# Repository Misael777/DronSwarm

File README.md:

# DronSwarm

Proyecto mecatrónico para diseñar y fabricar drones propios de bajo costo para minería y operarlos en enjambre con control avanzado.

- **DS-I (inspección):** compite con DJI Matrice 4E. Target: ≤ US$1,500, ≥ 35 min a 4,500 msnm, IP54.
- **DS-D (delivery):** compite con DJI Matrice 400. Target: ≤ US$3,500, 5 kg a 4,500 msnm.
- **Diferenciadores:** operación a ≥ 5,000 msnm, enjambre nativo, ecosistema abierto (PX4), sin licencias.

## Probar

```bash
./dronswarm.sh        # consola de pruebas: simulaciones, CAD, plan y diagnóstico
```
Detalle en [docs/como-probar.md](docs/como-probar.md).

## Documentos clave

| Documento | Para qué |
|---|---|
| [docs/plan/DronSwarm_Plan_de_Trabajo.xlsx](docs/plan/DronSwarm_Plan_de_Trabajo.xlsx) | Seguimiento del plan (24 sprints) |
| [docs/plan/PLAN_DE_TRABAJO.md](docs/plan/PLAN_DE_TRABAJO.md) | Plan técnico detallado |
| [docs/guia-estructura-repo.md](docs/guia-estructura-repo.md) | Estructura y convenciones |
| [docs/decisiones.md](docs/decisiones.md) | Decisiones técnicas (ADR) |
| [docs/setup-wsl.md](docs/setup-wsl.md) | Instalación del entorno |

## Estructura

`engineering/` cálculos · `simulation/` PX4 + Gazebo · `control/` enjambre y misiones · `cad/` OpenSCAD + FreeCAD ·
`electronics/` · `manufacturing/` · `hardware/` · `app/` · `tools/` · `docs/`

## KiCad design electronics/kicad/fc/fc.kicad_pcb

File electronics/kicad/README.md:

# E6 · Placas en KiCad

> Flujo: esquema SKIDL → netlist (`electronics/build_netlists.sh`) → placa (`make_boards.py`) → ruteo (`route_boards.py`,
> Freerouting) → DRC (`kicad-cli`) → fabricación (`fab_outputs.sh`, se niega si el DRC no está limpio).
> Abrir cada placa con KiCad 8: `electronics/kicad/<placa>/<placa>.kicad_pro` (la biblioteca `DronSwarm` se carga sola).

## Estado (2026-10-26)

| Placa | Piezas | Contorno actual · meta [mm] | Estado | Falta |
|---|---|---|---|---|
| GNSS (`gnss`) | 32 | 40 × 40 · 40 × 40 | **ruteada**: 0 errores de DRC, 1 conexión de 3V3 por cerrar; RF en microcinta de 0.36 mm ruteada a mano por script | cerrar 1 conexión, revisión humana, Gerber |
| BMS 6S (`bms_ds_i`) | 105 | 60 × 51 · 60 × 40 | colocada, nets asignadas | ruteo manual (el autorruteador dejó 27 pendientes) |
| BMS 12S (`bms_ds_d`) | 141 | 80 × 46 · 80 × 45 | colocada, nets asignadas | ruteo manual (el autorruteador no terminó en 1 h) |
| Controladora (`fc`) | 165 | 55 × 73 · 55 × 45 | colocada en dos caras, nets asignadas | colocación densa con conectores al borde y ruteo manual |
| ESC 4 en 1 DS-I (`esc_ds_i`) | 335 | 60 × 88 · 60 × 60 | colocada, nets asignadas | colocación de potencia (transistores en dos caras) y ruteo manual |
| ESC GaN DS-D (`esc_ds_d`) | 115 | 40 × 70 · 40 × 70 | colocada; **faltan las 3 huellas del LMG1210** | plano RVR0019A de TI, colocación del lazo GaN, ruteo manual |
| Cargador GaN (`charger`) | 131 | 100 × 80 · 100 × 80 | colocada; **faltan las 2 huellas del LMG1210** | ídem |

La colocación automática agrupa por subcircuito y pone los pasivos chicos abajo, pero **no está optimizada**: es el
punto de partida para colocar a mano en KiCad. El ruteo automático sirve para placas chicas de señal (GNSS); en las de
potencia y en las densas no converge y además no conviene: el lazo de conmutación se rutea a mano.

## Biblioteca `DronSwarm.pretty` (`gen_footprints.py`, desde las hojas de datos)

| Huella | Fuente |
|---|---|
| `EPC2302_QFN-3x5mm` | EPC2302: cobre, aberturas de máscara (máscara definida por soldadura) y esténcil, págs. 11-12 |
| `Bosch_LGA-16_3x4.5mm_P0.5mm` | BMI088, fig. 11 |
| `Quectel_LG290P_LGA-79_12.2x16mm` | LG290P(03) Hardware Design, fig. 18 (cortesía de 3 mm alrededor del módulo, como pide Quectel) |
| `Pad_Power_4x3mm`, `6x4mm`, `8x5mm` | pads para soldar cables de potencia |
| **`TI_WQFN-19_RVR0019A_4x3mm`** | **PENDIENTE**: la hoja SNOSD12D del LMG1210 no trae el dibujo mecánico; bajar el plano RVR0019A desde la página del producto en ti.com y agregarlo a `gen_footprints.py` |

## Reglas de las placas

- 4 capas: señal / GND (In1) / alimentación (In2) / señal. Clase **Potencia** 1.0 mm; **RF50** 0.36 mm (GNSS).
- **Placas de 12S a 5,000 msnm** (ESC DS-D, BMS DS-D, cargador): IPC-2221 pide 1.5 mm entre conductores de 51-100 V
  sin recubrimiento por encima de 3,050 m (B3); con **recubrimiento conformado** (B4) bastan 0.13 mm → el recubrimiento
  es obligatorio y está en el presupuesto.
- Lazo de potencia GaN (ESC DS-D, cargador): diseño "vertical" de EPC, con los condensadores de 2.2 µF en la cara
  opuesta, directamente bajo el medio puente, y retorno por In1 (nota de aplicación de EPC sobre el ruteo de GaN).

## Revisión humana antes de fabricar (cada placa)

1. DRC limpio y 0 conexiones pendientes; `bash electronics/kicad/fab_outputs.sh <placa>`.
2. Huellas propias impresas a 1:1 sobre la pieza real.
3. Potencia: ancho de pistas por corriente (IPC-2152), vías térmicas bajo transistores y LDO.
4. RF (GNSS): microcinta de 50 Ω con el stack real del fabricante, plano de GND continuo bajo la línea.
5. Distancias de 12S y recubrimiento conformado anotados en el plano de fabricación.

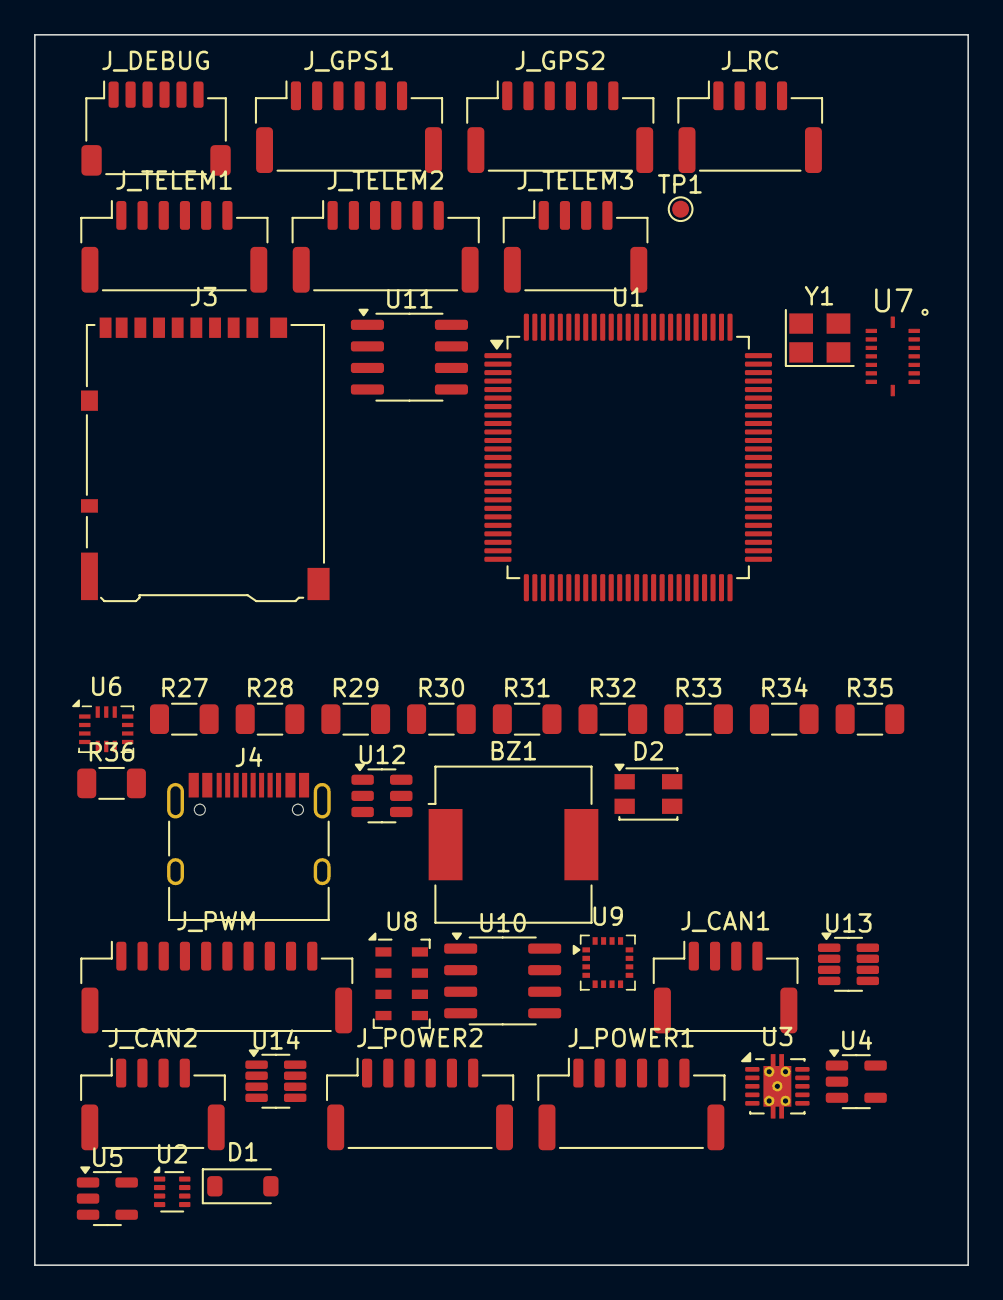
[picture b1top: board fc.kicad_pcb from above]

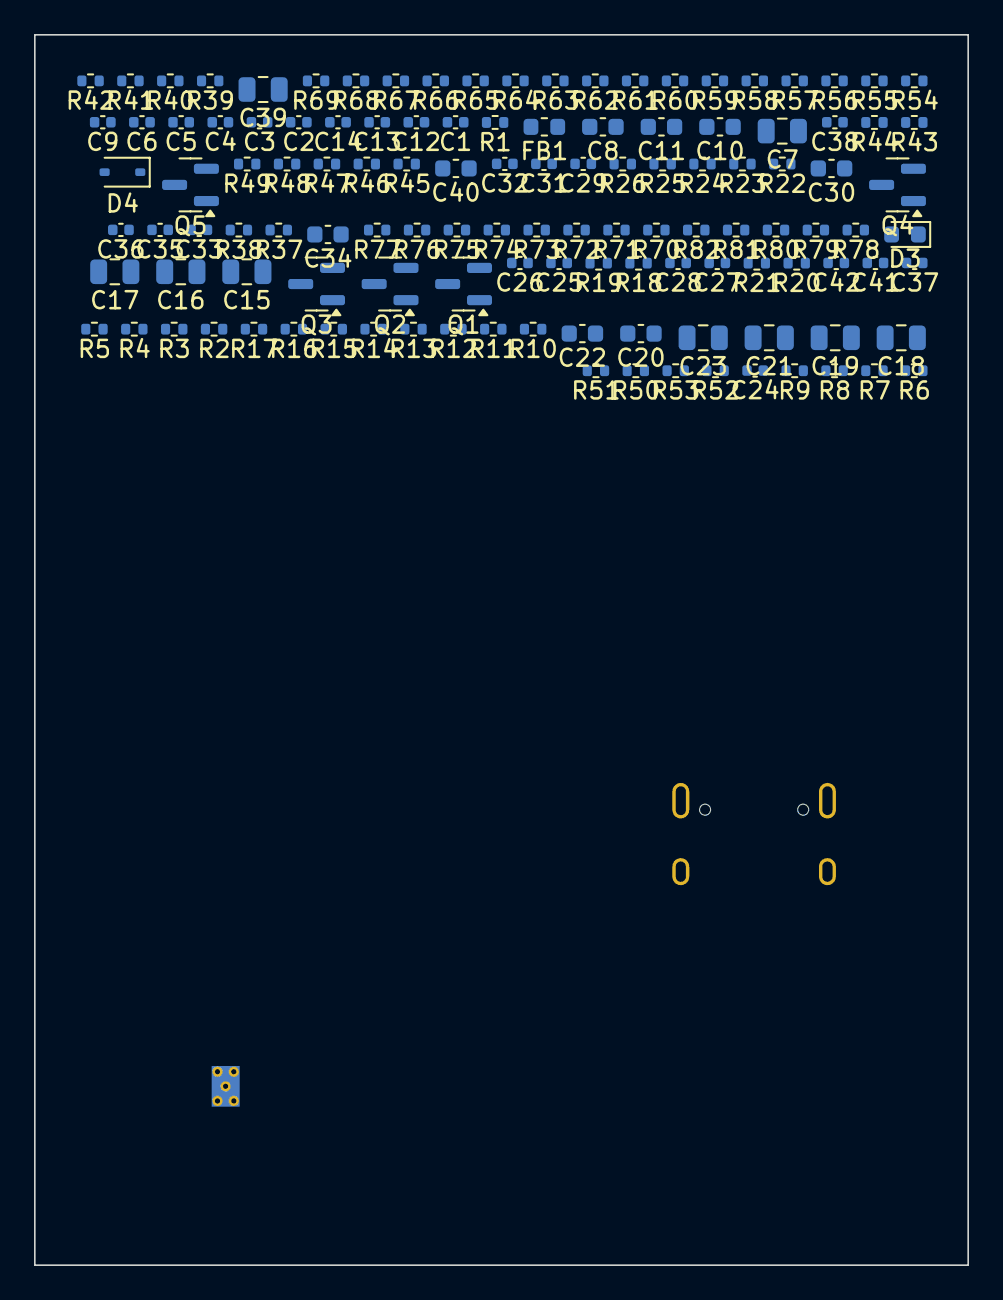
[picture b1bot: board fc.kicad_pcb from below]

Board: 4 copper layers, 55.0 x 72.5 mm, 165 parts (122 on the bottom side), 141 nets, no tracks yet.

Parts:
BZ1: Buzzer; Buzzer_CUI_CPT-9019S-SMT
C1, C2, C3, C4, C5, C6, C9, C12, C24, C25, C26, C27, C28, C29, C31, C32, C33, C35, C36, C37, C38, C41, C42: 100n; C_0402_1005Metric
C7: 4.7u; C_0805_2012Metric
C8, C20, C22, C34: 1u; C_0603_1608Metric
C10, C11, C30: 2.2u; C_0603_1608Metric
C13, C14: 12p/C0G; C_0402_1005Metric
C15, C16, C21, C23, C39: 10u/10V; C_0805_2012Metric
C17, C18, C19: 22u/10V; C_0805_2012Metric
C40: 4.7n/100V; C_0603_1608Metric
D1: PMEG2010; D_SOD-123
D2: LED_RGB; LED_Kingbright_AAA3528ESGCT
D3: verde; LED_0603_1608Metric
D4: BAT54; D_SOD-323
FB1: 600R@100MHz; L_0603_1608Metric
J3: Micro_SD_Card_Det1; microSD_HC_Hirose_DM3AT-SF-PEJM5
J4: USB_C_Receptacle_USB2.0_16P; USB_C_Receptacle_HRO_TYPE-C-31-M-12
J_CAN1, J_CAN2: Conn_01x04; JST_GH_SM04B-GHS-TB_1x04-1MP_P1.25mm_Horizontal
J_DEBUG: Conn_01x06; JST_SH_SM06B-SRSS-TB_1x06-1MP_P1.00mm_Horizontal
J_GPS1, J_GPS2: Conn_01x06; JST_GH_SM06B-GHS-TB_1x06-1MP_P1.25mm_Horizontal
J_POWER1, J_POWER2: Conn_01x06; JST_GH_SM06B-GHS-TB_1x06-1MP_P1.25mm_Horizontal
J_PWM: Conn_01x10; JST_GH_SM10B-GHS-TB_1x10-1MP_P1.25mm_Horizontal
J_RC: Conn_01x04; JST_GH_SM04B-GHS-TB_1x04-1MP_P1.25mm_Horizontal
J_TELEM1, J_TELEM2: Conn_01x06; JST_GH_SM06B-GHS-TB_1x06-1MP_P1.25mm_Horizontal
J_TELEM3: Conn_01x04; JST_GH_SM04B-GHS-TB_1x04-1MP_P1.25mm_Horizontal
Q1, Q2, Q3, Q5: 2N7002; SOT-23
Q4: AO3400A; SOT-23
R1, R3, R4, R5, R6, R7, R8, R9, R13, R14, R16, R17, R22, R23, R24, R39: 10k; R_0402_1005Metric
R2: 35.7k; R_0402_1005Metric
R10: 56k; R_0402_1005Metric
R11, R12, R15, R26, R82: 100k; R_0402_1005Metric
R18, R19, R20, R21, R78, R79, R80: 1k; R_0402_1005Metric
R25, R81: 100; R_0402_1005Metric
R27, R28, R29, R30, R31, R32, R33, R34, R35, R36: 150; R_1206_3216Metric
R37, R38, R50, R51, R52, R53: 2.2k; R_0402_1005Metric
R40, R41, R42, R43, R44: 47k; R_0402_1005Metric
R45, R46: 5.1k; R_0402_1005Metric
R47: 1M; R_0402_1005Metric
R48: 22k; R_0402_1005Metric
R49: 33k; R_0402_1005Metric
R54, R55, R56, R57, R58, R59, R60, R61, R62, R63, R64, R65, R66, R67, R68, R69: 22; R_0402_1005Metric
R70, R71, R72, R73, R74, R75, R76, R77: 47; R_0402_1005Metric
TP1: TestPoint; TestPoint_Pad_D1.0mm
U1: STM32H743VITx; LQFP-100_14x14mm_P0.5mm
U2: TPS2116DRL; SOT-583-8
U3: TPS2561; VSON-10-1EP_3x3mm_P0.5mm_EP1.65x2.4mm_ThermalVias
U4, U5: TLV75533PDBV; SOT-23-5
U6: IIM-42652; Bosch_LGA-14_3x2.5mm_P0.5mm
U7: BMI088; Bosch_LGA-16_3x4.5mm_P0.5mm
U8: MS5611-01BA; LGA-8_3x5mm_P1.25mm
U9: IST8310; LGA-16_3x3mm_P0.5mm
U10: 24LC64; SOIC-8_3.9x4.9mm_P1.27mm
U11: MB85RS256B; SOIC-8_3.9x4.9mm_P1.27mm
U12: USBLC6-2SC6; SOT-23-6
U13, U14: TCAN330; SOT-23-8
Y1: 16MHz 10pF; Crystal_SMD_3225-4Pin_3.2x2.5mm

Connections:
3V3: C1.1, C2.1, C3.1, C4.1, C5.1, C6.1, C7.1, C21.1, C38.1, C39.1, C41.1, C42.1, D2.4, FB1.1, J3.4, J_DEBUG.1, R13.2, R14.2, R39.2, R40.2, R41.2, R42.2, R43.2, R44.2, R50.2, R51.2, R52.2, R53.2, R80.1, U1.6, U1.11, U1.27, U1.50, U1.75, U1.100, U4.5, U11.3, U11.7, U11.8, U13.3, U14.3
3V3_SENSORS: C23.1, C29.1, C30.1, C31.1, C32.1, C33.1, C36.1, C37.1, R22.2, R23.2, R24.2, R37.2, R38.2, U5.5, U6.5, U6.8, U7.3, U7.11, U8.1, U8.2, U9.2, U9.13, U9.14, U10.8
5V: BZ1.1, C17.1, C20.1, C22.1, D1.1, D4.1, R16.1, R27.1, R28.1, R29.1, R30.1, R31.1, R32.1, R33.1, R34.1, R35.1, R36.1, U2.2, U2.7, U3.2, U3.3, U4.1, U4.3, U5.1
5V_HIPOWER: C19.1, J_CAN1.1, J_CAN2.1, U3.8
5V_PERIPH: C18.1, J_GPS1.1, J_GPS2.1, J_RC.1, J_TELEM1.1, J_TELEM2.1, J_TELEM3.1, U3.9
BATT1_I: J_POWER1.3, R18.1
BATT1_I_ADC: C25.1, R18.2, U1.32
BATT1_V: J_POWER1.4, R19.1
BATT1_V_ADC: C26.1, R19.2, U1.33
BATT2_I: J_POWER2.3, R20.1
BATT2_I_ADC: C27.1, R20.2, U1.24
BATT2_V: J_POWER2.4, R21.1
BATT2_V_ADC: C28.1, R21.2, U1.35
BRICK1_5V: C15.1, J_POWER1.1, J_POWER1.2, R2.1, R4.1, U2.3, U2.5
BRICK2_5V: C16.1, J_POWER2.1, J_POWER2.2, R6.1, U2.6
BUZZ_D: BZ1.2, D4.2, Q5.3
BUZZ_G: Q5.1, R81.2, R82.1
CAN1_H: J_CAN1.2, U13.7
CAN1_L: J_CAN1.3, U13.6
CAN2_H: J_CAN2.2, U14.7
CAN2_L: J_CAN2.3, U14.6
DET_BRICK1_5V: Q1.1, R4.2, R5.1
DET_BRICK2_5V: Q2.1, R6.2, R7.1
DET_USB_VBUS: Q3.1, R8.2, R9.1
GND: C1.2, C2.2, C3.2, C4.2, C5.2, C6.2, C7.2, C8.2, C9.2, C10.2, C11.2, C12.2, C13.2, C14.2, C15.2, C16.2, C17.2, C18.2, C19.2, C20.2, C21.2, C22.2, C23.2, C24.2, C25.2, C26.2, C27.2, C28.2, C29.2, C30.2, C31.2, C32.2, C33.2, C34.2, C35.2, C36.2, C37.2, C38.2, C39.2, C40.2, C41.2, C42.2, D3.1, J3.6, J3.10, J4.A1, J4.A12, J4.B1, J4.B12, J_CAN1.4, J_CAN2.4, J_DEBUG.6, J_GPS1.6, J_GPS2.6, J_POWER1.5, J_POWER1.6, J_POWER2.5, J_POWER2.6, J_PWM.9, J_PWM.10, J_RC.4, J_TELEM1.6, J_TELEM2.6, J_TELEM3.4, Q1.2, Q2.2, Q3.2, Q4.2, Q5.2, R1.2, R3.2, R5.2, R7.2, R9.2, R10.2, R11.2, R12.2, R15.2, R17.2, R26.2, R45.2, R46.2, R47.2, R49.2, R82.2, U1.10, U1.19, U1.26, U1.49, U1.74, U1.99, U2.1, U3.1, U3.11, U4.2, U5.2, U6.6, U6.7, U7.2, U7.4, U7.6, U7.7, U8.3, U8.4, U8.5, U9.5, U9.6, U9.9, U9.11, U10.1, U10.2, U10.3, U10.4, U10.7, U11.4, U12.2, U13.2, U13.5, U13.8, U14.2, U14.5, U14.8, Y1.2, Y1.4
HEATER_D: Q4.3, R27.2, R28.2, R29.2, R30.2, R31.2, R32.2, R33.2, R34.2, R35.2, R36.2
HEATER_G: Q4.1, R25.2, R26.1
HSE_IN: C13.1, U1.12, Y1.1
HSE_OUT: C14.1, U1.13, Y1.3
I2C1_SCL: J_GPS1.4, R50.1, U1.95
I2C1_SDA: J_GPS1.5, R51.1, U1.93
I2C2_SCL: J_GPS2.4, R52.1, U1.46
I2C2_SDA: J_GPS2.5, R53.1, U1.47
I2C4_SCL: R37.1, U1.59, U8.8, U9.1, U10.6
I2C4_SDA: R38.1, U1.60, U8.7, U9.16, U10.5
J_GPS1_PA10: J_GPS1.3, R65.2
J_GPS1_PB6: J_GPS1.2, R64.2
J_GPS2_PE0: J_GPS2.3, R67.2
J_GPS2_PE1: J_GPS2.2, R66.2
J_RC_PC6: J_RC.2, R68.2
J_RC_PC7: J_RC.3, R69.2
J_TELEM1_PE7: J_TELEM1.3, R55.2
J_TELEM1_PE8: J_TELEM1.2, R54.2
J_TELEM1_PE9: J_TELEM1.5, R57.2
J_TELEM1_PE10: J_TELEM1.4, R56.2
J_TELEM2_PC8: J_TELEM2.5, R61.2
J_TELEM2_PC9: J_TELEM2.4, R60.2
J_TELEM2_PC12: J_TELEM2.2, R58.2
J_TELEM2_PD2: J_TELEM2.3, R59.2
J_TELEM3_PA3: J_TELEM3.3, R63.2
J_TELEM3_PD5: J_TELEM3.2, R62.2
MUX_PR1: R2.2, R3.1, U2.4
unnamed: R1.1, U1.94
unnamed: Q1.3, U1.77
unnamed: Q2.3, U1.51
unnamed: Q3.3, U1.45
unnamed: R10.1, U3.7
unnamed: R11.1, U1.1, U3.4
unnamed: R12.1, U1.78, U3.5
unnamed: R13.1, U1.2, U3.10
unnamed: R14.1, U1.79, U3.6
unnamed: R15.1, U1.36, U5.3
unnamed: R22.1, U1.7, U6.12
unnamed: U1.5, U6.4
unnamed: R24.1, U1.9, U7.14
unnamed: R23.1, U1.8, U7.5
unnamed: U1.3, U7.16
unnamed: U1.4, U7.12
unnamed: R25.1, U1.96
unnamed: C34.1, U9.10
unnamed: C35.1, U9.7
unnamed: R39.1, U1.85, U11.1
unnamed: U1.84, U11.6
unnamed: U1.18, U11.5
unnamed: U1.17, U11.2
unnamed: J3.5, U1.87
unnamed: J3.3, R40.1, U1.88
unnamed: J3.7, R41.1, U1.53
unnamed: J3.8, R42.1, U1.54
unnamed: J3.1, R43.1, U1.89
unnamed: J3.2, R44.1, U1.90
unnamed: J4.A5, R45.1
unnamed: J4.B5, R46.1
unnamed: U1.82, U13.1
unnamed: U1.81, U13.4
unnamed: U1.52, U14.1
unnamed: U1.91, U14.4
unnamed: R54.1, U1.38
unnamed: R55.1, U1.37
unnamed: R56.1, U1.40
unnamed: R57.1, U1.39
unnamed: R58.1, U1.80
unnamed: R59.1, U1.83
unnamed: R60.1, U1.66
unnamed: R61.1, U1.65
unnamed: R62.1, U1.86
unnamed: R63.1, U1.25
unnamed: R64.1, U1.92
unnamed: R65.1, U1.69
unnamed: R66.1, U1.98
unnamed: R67.1, U1.97
unnamed: R68.1, U1.63
unnamed: R69.1, U1.64
unnamed: J_DEBUG.2, U1.55
unnamed: J_DEBUG.3, U1.56
unnamed: J_DEBUG.4, U1.72
unnamed: J_DEBUG.5, U1.76
unnamed: R70.1, U1.67
unnamed: R71.1, U1.41
unnamed: R72.1, U1.43
unnamed: R73.1, U1.44
unnamed: R74.1, U1.61
unnamed: R75.1, U1.62
unnamed: R76.1, U1.22
unnamed: R77.1, U1.23
unnamed: D2.1, R78.1
unnamed: R78.2, U1.57
unnamed: D2.3, R79.1
unnamed: R79.2, U1.58
unnamed: D3.2, R80.2
unnamed: R81.1, U1.34
NRST: C12.1, TP1.1, U1.14
PWM1: J_PWM.1, R70.2
PWM2: J_PWM.2, R71.2
PWM3: J_PWM.3, R72.2
PWM4: J_PWM.4, R73.2
PWM5: J_PWM.5, R74.2
PWM6: J_PWM.6, R75.2
PWM7: J_PWM.7, R76.2
PWM8: J_PWM.8, R77.2
SCALED_V5: C24.1, R16.2, R17.1, U1.28
SPI1_MISO: U1.30, U6.1, U7.10, U7.15
SPI1_MOSI: U1.31, U6.14, U7.9
SPI1_SCK: U1.29, U6.13, U7.8
USB_DM: J4.A7, J4.B7, U1.70, U12.3, U12.4
USB_DP: J4.A6, J4.B6, U1.71, U12.1, U12.6
USB_SHIELD: C40.1, J4.S1, R47.1
USB_VBUS: D1.2, J4.A4, J4.A9, J4.B4, J4.B9, R8.1, R48.1, U12.5
USB_VBUS_SENSE: R48.2, R49.1, U1.68
VCAP: C10.1, C11.1, U1.48, U1.73
VDDA: C8.1, C9.1, FB1.2, U1.20, U1.21

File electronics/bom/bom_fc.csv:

Comment,Designator,Footprint,Quantity,Unit price USD (est.)
100n,"C1,C2,C3,C4,C5,C6,C9,C12,C24,C25,C26,C27,C28,C29,C31,C32,C33,C35,C36,C37,C38,C41,C42",Capacitor_SMD:C_0402_1005Metric,23,0.004
10k,"R1,R3,R4,R5,R6,R7,R8,R9,R13,R14,R16,R17,R22,R23,R24,R39",Resistor_SMD:R_0402_1005Metric,16,0.002
22,"R54,R55,R56,R57,R58,R59,R60,R61,R62,R63,R64,R65,R66,R67,R68,R69",Resistor_SMD:R_0402_1005Metric,16,0.002
150,"R27,R28,R29,R30,R31,R32,R33,R34,R35,R36",Resistor_SMD:R_1206_3216Metric,10,0.008
47,"R70,R71,R72,R73,R74,R75,R76,R77",Resistor_SMD:R_0402_1005Metric,8,0.002
1k,"R18,R19,R20,R21,R78,R79,R80",Resistor_SMD:R_0402_1005Metric,7,0.002
2.2k,"R37,R38,R50,R51,R52,R53",Resistor_SMD:R_0402_1005Metric,6,0.002
Conn_01x06,"J_GPS1,J_GPS2,J_POWER1,J_POWER2,J_TELEM1,J_TELEM2",Connector_JST:JST_GH_SM06B-GHS-TB_1x06-1MP_P1.25mm_Horizontal,6,0.24
100k,"R11,R12,R15,R26,R82",Resistor_SMD:R_0402_1005Metric,5,0.002
10u/10V,"C15,C16,C21,C23,C39",Capacitor_SMD:C_0805_2012Metric,5,0.03
47k,"R40,R41,R42,R43,R44",Resistor_SMD:R_0402_1005Metric,5,0.002
1u,"C8,C20,C22,C34",Capacitor_SMD:C_0603_1608Metric,4,0.008
2N7002,"Q1,Q2,Q3,Q5",Package_TO_SOT_SMD:SOT-23,4,0.02
Conn_01x04,"J_CAN1,J_CAN2,J_RC,J_TELEM3",Connector_JST:JST_GH_SM04B-GHS-TB_1x04-1MP_P1.25mm_Horizontal,4,0.2
2.2u,"C10,C11,C30",Capacitor_SMD:C_0603_1608Metric,3,0.008
22u/10V,"C17,C18,C19",Capacitor_SMD:C_0805_2012Metric,3,0.03
100,"R25,R81",Resistor_SMD:R_0402_1005Metric,2,0.002
12p/C0G,"C13,C14",Capacitor_SMD:C_0402_1005Metric,2,0.004
5.1k,"R45,R46",Resistor_SMD:R_0402_1005Metric,2,0.002
TCAN330,"U13,U14",Package_TO_SOT_SMD:SOT-23-8,2,0.9
TLV75533PDBV,"U4,U5",Package_TO_SOT_SMD:SOT-23-5,2,0.12
16MHz 10pF,Y1,Crystal:Crystal_SMD_3225-4Pin_3.2x2.5mm,1,0.12
1M,R47,Resistor_SMD:R_0402_1005Metric,1,0.002
22k,R48,Resistor_SMD:R_0402_1005Metric,1,0.002
24LC64,U10,Package_SO:SOIC-8_3.9x4.9mm_P1.27mm,1,0.15
33k,R49,Resistor_SMD:R_0402_1005Metric,1,0.002
35.7k,R2,Resistor_SMD:R_0402_1005Metric,1,0.002
4.7n/100V,C40,Capacitor_SMD:C_0603_1608Metric,1,0.008
4.7u,C7,Capacitor_SMD:C_0805_2012Metric,1,0.03
56k,R10,Resistor_SMD:R_0402_1005Metric,1,0.002
600R@100MHz,FB1,Inductor_SMD:L_0603_1608Metric,1,0.01
AO3400A,Q4,Package_TO_SOT_SMD:SOT-23,1,0.03
BAT54,D4,Diode_SMD:D_SOD-323,1,0.03
BMI088,U7,DronSwarm:Bosch_LGA-16_3x4.5mm_P0.5mm,1,5.5
Buzzer,BZ1,Buzzer_Beeper:Buzzer_CUI_CPT-9019S-SMT,1,0.4
Conn_01x06,J_DEBUG,Connector_JST:JST_SH_SM06B-SRSS-TB_1x06-1MP_P1.00mm_Horizontal,1,0.12
Conn_01x10,J_PWM,Connector_JST:JST_GH_SM10B-GHS-TB_1x10-1MP_P1.25mm_Horizontal,1,0.32
IIM-42652,U6,Package_LGA:Bosch_LGA-14_3x2.5mm_P0.5mm,1,4.5
IST8310,U9,Package_LGA:LGA-16_3x3mm_P0.5mm,1,0.8
LED_RGB,D2,LED_SMD:LED_Kingbright_AAA3528ESGCT,1,0.02
MB85RS256B,U11,Package_SO:SOIC-8_3.9x4.9mm_P1.27mm,1,1.6
MS5611-01BA,U8,Package_LGA:LGA-8_3x5mm_P1.25mm,1,3.5
Micro_SD_Card_Det1,J3,Connector_Card:microSD_HC_Hirose_DM3AT-SF-PEJM5,1,0.25
PMEG2010,D1,Diode_SMD:D_SOD-123,1,0.03
STM32H743VITx,U1,Package_QFP:LQFP-100_14x14mm_P0.5mm,1,9.8
TPS2116DRL,U2,Package_TO_SOT_SMD:SOT-583-8,1,0.45
TPS2561,U3,Package_SON:VSON-10-1EP_3x3mm_P0.5mm_EP1.65x2.4mm_ThermalVias,1,0.9
TestPoint,TP1,TestPoint:TestPoint_Pad_D1.0mm,1,0.0
USBLC6-2SC6,U12,Package_TO_SOT_SMD:SOT-23-6,1,0.1
USB_C_Receptacle_USB2.0_16P,J4,Connector_USB:USB_C_Receptacle_HRO_TYPE-C-31-M-12,1,0.15
verde,D3,LED_SMD:LED_0603_1608Metric,1,0.02

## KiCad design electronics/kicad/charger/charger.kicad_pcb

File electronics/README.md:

# Electrónica propia DronSwarm (S20-S22)

Plan y estado: [PLAN.md](PLAN.md) · decisiones: ADR-015 y ADR-016 en `docs/decisiones.md`.

| Carpeta | Contenido |
|---|---|
| `requisitos/` | E0: requisitos eléctricos (generado por `calculo/requisitos.py`) |
| `calculo/` | E1 GaN vs silicio, E3 decisión del ESC del DS-I, packs de batería y cargador |
| `informes/` | Informes generados (E1, E3, E5, S20-07) |
| `skidl/` | Esquemas como código (SKIDL): `esc_ds_d`, `esc_ds_i`, `fc`, `gnss`, `bms`, `charger` + bloques y piezas propias |
| `kicad/` | Netlists, biblioteca `DronSwarm.pretty`, placas KiCad, ruteo y archivos de fabricación (ver `kicad/README.md`) |
| `fc/` | Target de PX4 `dronswarm_fmu-v1` y su documentación |
| `bom/` | E7: listas de materiales por placa y `Presupuesto_Electronica.xlsx` |
| `pruebas/` | E8: procedimientos de fabricación, banco, HITL, GNSS e integración |
| `tests/` | Pruebas de las netlists contra hojas de datos y el port de PX4 |

```bash
bash electronics/build_netlists.sh                       # esquemas → netlists (ERC)
source ~/.local/opt/kicad8/env.sh
/usr/bin/python3 electronics/kicad/gen_footprints.py      # huellas propias
/usr/bin/python3 electronics/kicad/make_boards.py         # placas desde las netlists
/usr/bin/python3 electronics/kicad/route_boards.py gnss   # ruteo automático + DRC
bash electronics/kicad/fab_outputs.sh gnss                # Gerber, taladros, posiciones, BOM
bash electronics/fc/build_px4.sh                          # firmware PX4 de la controladora
.venv/bin/python electronics/bom/gen_presupuesto.py      # presupuesto
.venv/bin/pytest -q electronics/tests
```

Herramientas locales sin sudo: KiCad 8.0.9 en `~/.local/opt/kicad8` (paquetes del PPA oficial, firma verificada),
GCC ARM 9-2020-q2 en `~/.local/opt/`, Freerouting 2.5 con JRE 25 en `~/.local/opt/`.

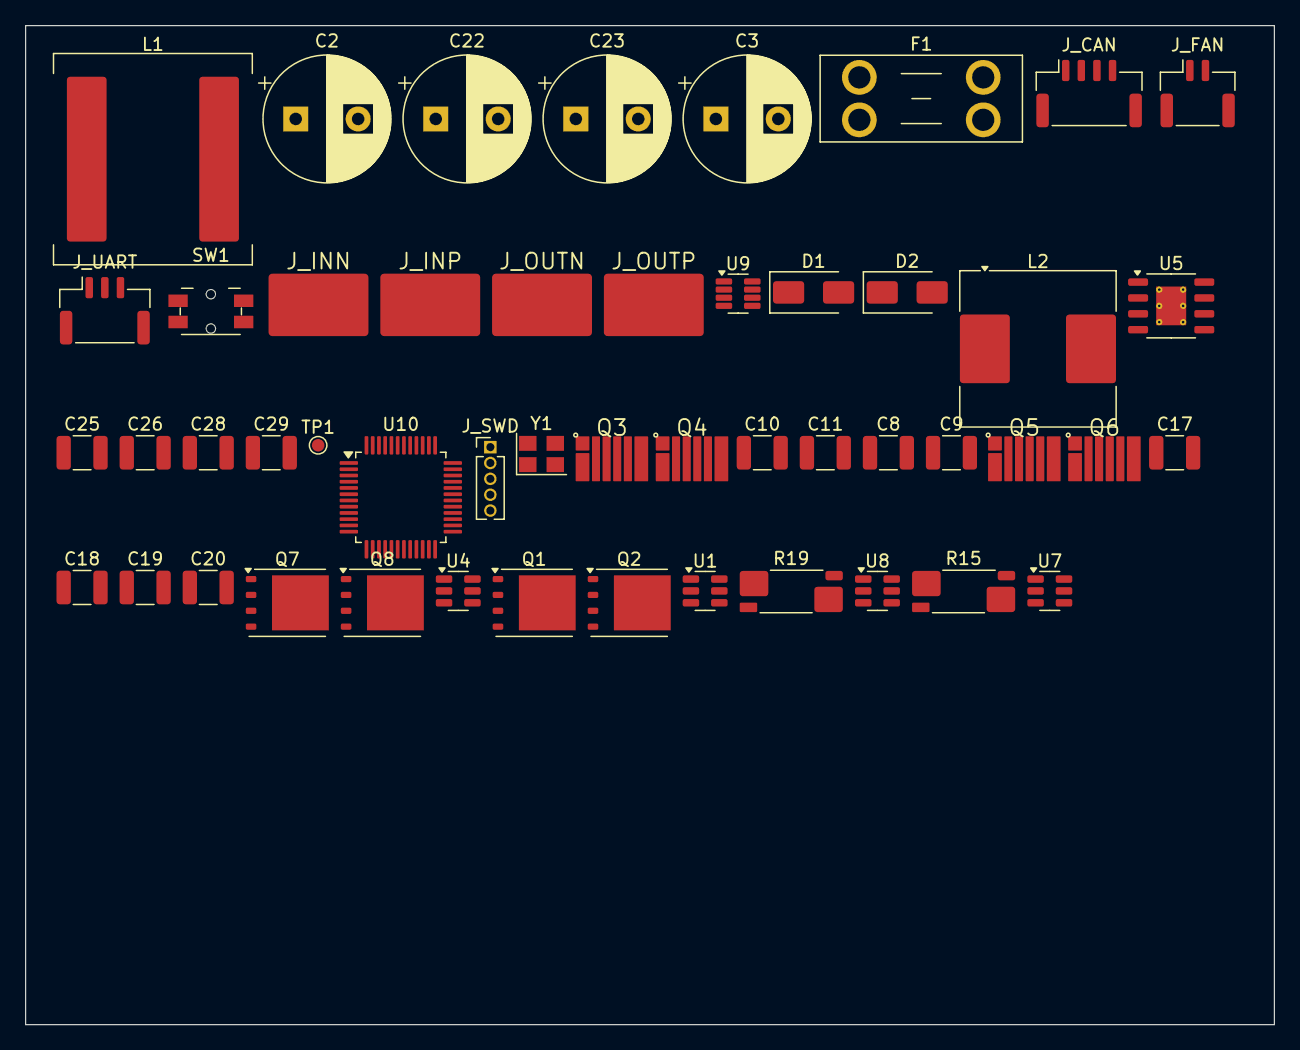
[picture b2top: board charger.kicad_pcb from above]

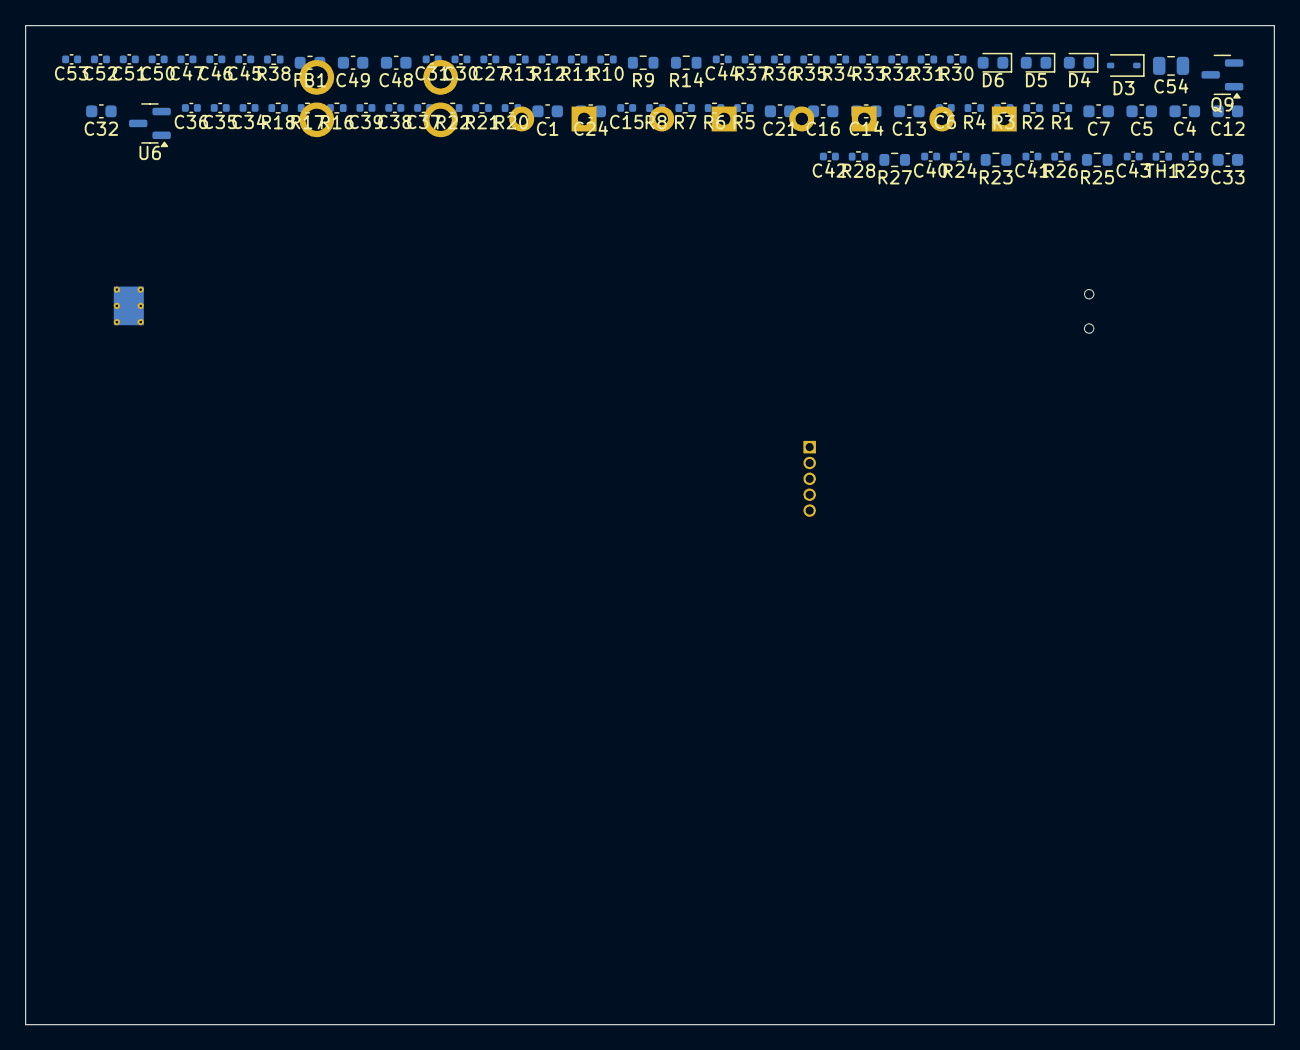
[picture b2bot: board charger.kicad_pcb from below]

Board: 4 copper layers, 100.0 x 80.0 mm, 131 parts (82 on the bottom side), 70 nets, no tracks yet.

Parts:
C1, C24: 220n/16V; C_0603_1608Metric
C2, C3, C22, C23: 470u/63V; CP_Radial_D10.0mm_P5.00mm
C4, C5, C13, C14, C32, C33, C49: 1u; C_0603_1608Metric
C6, C15, C34, C35, C36, C37, C38, C39, C40, C41, C42, C43, C44, C45, C46, C47, C50, C51: 100n; C_0402_1005Metric
C7, C16: 100n; C_0603_1608Metric
C8, C9, C10, C11, C17, C18, C19, C20, C25, C26: 2.2u/100V; C_1210_3225Metric
C12, C21: 100n/100V; C_0603_1608Metric
C27: 2.2n/50V; C_0402_1005Metric
C28, C29: 22u/25V; C_1210_3225Metric
C30: 3.3n; C_0402_1005Metric
C31: 56p/C0G; C_0402_1005Metric
C48: 4.7u; C_0603_1608Metric
C52, C53: 10p/C0G; C_0402_1005Metric
C54: 1u; C_0805_2012Metric
D1, D2: SMAJ58A; D_SMA
D3: BAT54; D_SOD-323
D4: rojo; LED_0603_1608Metric
D5, D6: verde; LED_0603_1608Metric
F1: 30A; Fuseholder_Blade_Mini_Keystone_3568
FB1: 600R@100MHz; L_0603_1608Metric
J_CAN: Conn_01x04; JST_GH_SM04B-GHS-TB_1x04-1MP_P1.25mm_Horizontal
J_FAN: Conn_01x02; JST_GH_SM02B-GHS-TB_1x02-1MP_P1.25mm_Horizontal
J_INN: Conn_01x01; Pad_Power_8x5mm
J_INP: Conn_01x01; Pad_Power_8x5mm
J_OUTN: Conn_01x01; Pad_Power_8x5mm
J_OUTP: Conn_01x01; Pad_Power_8x5mm
J_SWD: Conn_01x05; PinHeader_1x05_P1.27mm_Vertical
J_UART: Conn_01x03; JST_GH_SM03B-GHS-TB_1x03-1MP_P1.25mm_Horizontal
L1: 6.8u XAL1510-682; L_Coilcraft_XAL1510-682
L2: 68u; L_Coilcraft_MSS1246-XXX
Q1, Q2, Q7, Q8: BSC035N10NS5; TDSON-8-1
Q3, Q4, Q5, Q6: EPC2302; EPC2302_QFN-3x5mm
Q9: AO3400A; SOT-23
R1, R2, R5, R6: 2.2; R_0402_1005Metric
R3, R4, R7, R8, R24, R26, R28, R29, R34, R35, R36, R37, R38: 10k; R_0402_1005Metric
R9: 1M; R_0603_1608Metric
R10: 52.3k; R_0402_1005Metric
R11, R30: 100k; R_0402_1005Metric
R12: 453k; R_0402_1005Metric
R13: 49.9k; R_0402_1005Metric
R14: 453k; R_0603_1608Metric
R15, R19: 1m/3W; R_Shunt_Vishay_WSK2512_6332Metric_T1.19mm
R16, R17, R20, R21: 10; R_0402_1005Metric
R18, R22, R31, R32: 1k; R_0402_1005Metric
R23, R25, R27: 200k; R_0603_1608Metric
R33: 2.2k; R_0402_1005Metric
SW1: SW_Push; Panasonic_EVQPUL_EVQPUC
TH1: 10k B3950; R_0402_1005Metric
TP1: TestPoint; TestPoint_Pad_D1.0mm
U1, U4: LM74700; SOT-23-6
U5: LM5164DDA; HSOP-8-1EP_3.9x4.9mm_P1.27mm_EP2.41x3.1mm_ThermalVias
U6: MCP1703Ax-330xxTT; SOT-23
U7, U8: INA181A2; SOT-23-6
U9: TCAN330; SOT-23-8
U10: STM32G474CETx; LQFP-48_7x7mm_P0.5mm
Y1: 8MHz; Crystal_SMD_3225-4Pin_3.2x2.5mm

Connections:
3V3: C33.1, C35.1, C38.1, C44.1, C45.1, C46.1, C47.1, C48.1, FB1.1, J_SWD.1, R29.1, R33.1, U6.2, U7.6, U8.6, U9.3, U10.1, U10.24, U10.36, U10.48
12V: C4.1, C13.1, C28.1, C29.1, C30.2, C32.1, C54.1, D3.1, J_FAN.1, L2.2, R12.1, U6.3
BTN: SW1.1, U10.28
BUCK_EN: R9.2, R10.1, U5.3
BUCK_FB: C31.2, R12.2, R13.1, U5.5
BUCK_RA: C30.1, C31.1, R14.2
CAN_RX: U9.4, U10.33
CAN_TX: U9.1, U10.34
FAN_G: Q9.1, R30.1, U10.14
FAN_N: D3.2, J_FAN.2, Q9.3
GA_HI: Q3.1, R1.2, R3.1
GA_LO: Q4.1, R2.2, R4.1
GB_HI: Q5.1, R5.2, R7.1
GB_LO: Q6.1, R6.2, R8.1
GND: C2.2, C3.2, C4.2, C5.2, C6.2, C8.2, C9.2, C10.2, C11.2, C12.2, C13.2, C14.2, C15.2, C17.2, C18.2, C19.2, C20.2, C21.2, C22.2, C23.2, C25.2, C26.2, C28.2, C29.2, C32.2, C33.2, C35.2, C36.2, C38.2, C39.2, C40.2, C41.2, C42.2, C43.2, C44.2, C45.2, C46.2, C47.2, C48.2, C49.2, C50.2, C51.2, C52.2, C53.2, C54.2, D4.1, D5.1, D6.1, J_CAN.4, J_SWD.5, J_UART.1, Q4.2, Q4.4, Q4.6, Q6.2, Q6.4, Q6.6, Q9.2, R4.2, R8.2, R10.2, R11.2, R13.2, R15.1, R19.4, R24.2, R26.2, R28.2, R30.2, R34.2, R35.2, R36.2, R37.2, R38.2, SW1.2, TH1.2, U1.2, U4.2, U5.1, U5.9, U6.1, U7.2, U7.5, U8.2, U8.5, U9.2, U9.5, U9.8, U10.19, U10.23, U10.35, U10.47, Y1.2, Y1.4
IDEAL_G_VIN: Q1.4, Q2.4, U1.5
IDEAL_G_VOUT_D: Q7.4, Q8.4, U4.5
IN_N: D1.2, J_INN.1, R15.4
ISENSE_N: C34.2, R17.2, U7.4
ISENSE_N1: C37.2, R21.2, U8.4
ISENSE_P: C34.1, R16.2, U7.3
ISENSE_P1: C37.1, R20.2, U8.3
I_IN: C36.1, R18.2, U10.10
I_OUT: C39.1, R22.2, U10.11
LED_CHG: R32.1, U10.25
LED_CHG_A: D5.2, R32.2
LED_FAULT: R31.1, U10.22
LED_FAULT_A: D4.2, R31.2
unnamed: C1.1, U1.1
unnamed: C24.1, U4.1
unnamed: R11.1, U5.4
unnamed: C27.1, U5.7
unnamed: TP1.1, U5.6
unnamed: R15.2, R16.1
unnamed: R15.3, R17.1
unnamed: R18.1, U7.1
unnamed: R19.2, R20.1
unnamed: R19.3, R21.1
unnamed: R22.1, U8.1
unnamed: J_CAN.2, U9.7
unnamed: J_CAN.3, U9.6
unnamed: D6.2, R33.2
unnamed: R38.1, U10.45
unnamed: C52.1, U10.5, Y1.1
unnamed: C53.1, U10.6, Y1.3
unnamed: J_SWD.2, U10.37
unnamed: J_SWD.3, U10.38
NRST: C51.1, J_SWD.4, U10.7
OUT_N: D2.2, J_OUTN.1, R19.1
PWM_A_HI: R34.1, U10.30
PWM_A_LO: R35.1, U10.31
PWM_B_HI: R36.1, U10.26
PWM_B_LO: R37.1, U10.27
SW_A: C7.2, L1.1, Q3.2, Q3.4, Q3.6, Q4.3, Q4.5, Q4.7, R3.2
SW_B: C16.2, L1.2, Q5.2, Q5.4, Q5.6, Q6.3, Q6.5, Q6.7, R7.2
SW_BUCK: C27.2, L2.1, R14.1, U5.8
TEMP_SENSE: C43.1, R29.2, TH1.1, U10.16
UART_RX: J_UART.3, U10.44
UART_TX: J_UART.2, U10.43
VBUS_OUT_SENSE: C42.1, R27.2, R28.1, U10.12
VDD5_A: C5.1, C6.1
VDD5_B: C14.1, C15.1
VDDA: C49.1, C50.1, FB1.2, U10.20, U10.21
VIN: C2.1, C3.1, C8.1, C9.1, C10.1, C11.1, C12.1, C25.1, C26.1, Q1.5, Q2.5, Q3.3, Q3.5, Q3.7, R9.1, R23.1, U1.4, U5.2
VIN_RAW: C1.2, D1.1, J_INP.1, Q1.1, Q1.2, Q1.3, Q2.1, Q2.2, Q2.3, U1.3, U1.6
VIN_SENSE: C40.1, R23.2, R24.1, U10.8
VOUT: D2.1, F1.2, J_OUTP.1, R25.1
VOUT_D: F1.1, Q7.5, Q8.5, U4.4
VOUT_INT: C17.1, C18.1, C19.1, C20.1, C21.1, C22.1, C23.1, C24.2, Q5.3, Q5.5, Q5.7, Q7.1, Q7.2, Q7.3, Q8.1, Q8.2, Q8.3, R27.1, U4.3, U4.6
VOUT_SENSE: C41.1, R25.2, R26.1, U10.9

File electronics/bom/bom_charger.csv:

Comment,Designator,Footprint,Quantity,Unit price USD (est.)
100n,"C6,C15,C34,C35,C36,C37,C38,C39,C40,C41,C42,C43,C44,C45,C46,C47,C50,C51",Capacitor_SMD:C_0402_1005Metric,18,0.004
10k,"R3,R4,R7,R8,R24,R26,R28,R29,R34,R35,R36,R37,R38",Resistor_SMD:R_0402_1005Metric,13,0.002
2.2u/100V,"C8,C9,C10,C11,C17,C18,C19,C20,C25,C26",Capacitor_SMD:C_1210_3225Metric,10,0.15
1u,"C4,C5,C13,C14,C32,C33,C49",Capacitor_SMD:C_0603_1608Metric,7,0.008
10,"R16,R17,R20,R21",Resistor_SMD:R_0402_1005Metric,4,0.002
1k,"R18,R22,R31,R32",Resistor_SMD:R_0402_1005Metric,4,0.002
2.2,"R1,R2,R5,R6",Resistor_SMD:R_0402_1005Metric,4,0.002
470u/63V,"C2,C3,C22,C23",Capacitor_THT:CP_Radial_D10.0mm_P5.00mm,4,0.35
BSC035N10NS5,"Q1,Q2,Q7,Q8",Package_TO_SOT_SMD:TDSON-8-1,4,1.2
Conn_01x01,"J_INN,J_INP,J_OUTN,J_OUTP",DronSwarm:Pad_Power_8x5mm,4,0.0
EPC2302,"Q3,Q4,Q5,Q6",DronSwarm:EPC2302_QFN-3x5mm,4,4.0
200k,"R23,R25,R27",Resistor_SMD:R_0603_1608Metric,3,0.003
100k,"R11,R30",Resistor_SMD:R_0402_1005Metric,2,0.002
100n,"C7,C16",Capacitor_SMD:C_0603_1608Metric,2,0.008
100n/100V,"C12,C21",Capacitor_SMD:C_0603_1608Metric,2,0.008
10p/C0G,"C52,C53",Capacitor_SMD:C_0402_1005Metric,2,0.004
1m/3W,"R15,R19",Resistor_SMD:R_Shunt_Vishay_WSK2512_6332Metric_T1.19mm,2,0.35
220n/16V,"C1,C24",Capacitor_SMD:C_0603_1608Metric,2,0.008
22u/25V,"C28,C29",Capacitor_SMD:C_1210_3225Metric,2,0.12
INA181A2,"U7,U8",Package_TO_SOT_SMD:SOT-23-6,2,0.35
LM74700,"U1,U4",Package_TO_SOT_SMD:SOT-23-6,2,1.0
LMG1210,"U2,U3",DronSwarm:TI_WQFN-19_RVR0019A_4x3mm,2,3.0
SMAJ58A,"D1,D2",Diode_SMD:D_SMA,2,0.08
verde,"D5,D6",LED_SMD:LED_0603_1608Metric,2,0.02
10k B3950,TH1,Resistor_SMD:R_0402_1005Metric,1,0.03
1M,R9,Resistor_SMD:R_0603_1608Metric,1,0.003
1u,C54,Capacitor_SMD:C_0805_2012Metric,1,0.03
2.2k,R33,Resistor_SMD:R_0402_1005Metric,1,0.002
2.2n/50V,C27,Capacitor_SMD:C_0402_1005Metric,1,0.004
3.3n,C30,Capacitor_SMD:C_0402_1005Metric,1,0.004
30A,F1,Fuse:Fuseholder_Blade_Mini_Keystone_3568,1,0.3
4.7u,C48,Capacitor_SMD:C_0603_1608Metric,1,0.008
453k,R12,Resistor_SMD:R_0402_1005Metric,1,0.002
453k,R14,Resistor_SMD:R_0603_1608Metric,1,0.003
49.9k,R13,Resistor_SMD:R_0402_1005Metric,1,0.002
52.3k,R10,Resistor_SMD:R_0402_1005Metric,1,0.002
56p/C0G,C31,Capacitor_SMD:C_0402_1005Metric,1,0.004
6.8u XAL1510-682,L1,Inductor_SMD:L_Coilcraft_XAL1510-682,1,3.5
600R@100MHz,FB1,Inductor_SMD:L_0603_1608Metric,1,0.01
68u,L2,Inductor_SMD:L_Coilcraft_MSS1246-XXX,1,0.45
8MHz,Y1,Crystal:Crystal_SMD_3225-4Pin_3.2x2.5mm,1,0.12
AO3400A,Q9,Package_TO_SOT_SMD:SOT-23,1,0.03
BAT54,D3,Diode_SMD:D_SOD-323,1,0.03
Conn_01x02,J_FAN,Connector_JST:JST_GH_SM02B-GHS-TB_1x02-1MP_P1.25mm_Horizontal,1,0.16
Conn_01x03,J_UART,Connector_JST:JST_GH_SM03B-GHS-TB_1x03-1MP_P1.25mm_Horizontal,1,0.18
Conn_01x04,J_CAN,Connector_JST:JST_GH_SM04B-GHS-TB_1x04-1MP_P1.25mm_Horizontal,1,0.2
Conn_01x05,J_SWD,Connector_PinHeader_1.27mm:PinHeader_1x05_P1.27mm_Vertical,1,0.05
LM5164DDA,U5,Package_SO:HSOP-8-1EP_3.9x4.9mm_P1.27mm_EP2.41x3.1mm_ThermalVias,1,1.4
MCP1703Ax-330xxTT,U6,Package_TO_SOT_SMD:SOT-23,1,0.35
STM32G474CETx,U10,Package_QFP:LQFP-48_7x7mm_P0.5mm,1,4.5
SW_Push,SW1,Button_Switch_SMD:Panasonic_EVQPUL_EVQPUC,1,0.1
TCAN330,U9,Package_TO_SOT_SMD:SOT-23-8,1,0.9
TestPoint,TP1,TestPoint:TestPoint_Pad_D1.0mm,1,0.0
rojo,D4,LED_SMD:LED_0603_1608Metric,1,0.02
